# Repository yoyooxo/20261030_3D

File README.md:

# 20261030_3D — 讀卡機（單顆 nRF52840＋健保卡卡座）

只用一顆 nRF52840 模組（nice!nano v2 腳位）接 ISO 7816 卡座，焊在一塊 11 × 24 孔的洞洞板上。
卡座在板子背面、插卡口在上，模組的 USB-C 朝下，線全部在正面用 OK 線手焊，電池最後用雙面膠黏。

目前版本是 v7。

## 規格

| 項目 | 內容 |
|---|---|
| 洞洞板 | 27.9 × 61 mm，11 × 24 孔，2.54 mm 間距，直放 |
| 孔位標示 | (欄 c, 列 r)：c 為 1–11（左→右），r 為 1–24（下→上），正面俯視 |
| 卡座 J1 | 約 62 × 40 mm，在板子背面，上緣是插卡口；8 支腳焊進 c8–c11 的第 24 列和第 8 列 |
| 模組 U1 | 腳在 c1、c7 的第 1–12 列，轉 180°，USB-C 從板子下緣凸出；每邊 13 孔，最靠 USB 那對 B+ / B- 在板子外 |
| C10 | 0.1 µF，c8、c9 的第 6 列 |
| 電池 | LiPo 約 13 × 23 mm（照片估），在模組右邊，蓋在線上面 |

## 卡座腳位

| 位置 | c8 | c9 | c10 | c11 |
|---|---|---|---|---|
| 插卡口那排（第 24 列） | C5 GND | C6 | C7 I/O | C8 |
| 對面那排（第 8 列） | C1 VCC | C2 RST | C3 CLK | C4 |

C4、C6、C8 不接線，腳還是焊進洞，用來固定卡座。

## 接線（全部走正面，用 OK 線）

| 線號 | 起點 | 終點 | 用途 |
|---|---|---|---|
| K1 | VCC (c1,r4) | J1 C1 VCC (c8,r8) | +3V3_CARD，跨過模組，途中接 C10 |
| K2 | GND (c7,r3) | J1 C5 GND (c8,r24) | 卡片 GND |
| K3 | P0.24 (c7,r8) | J1 C2 RST (c9,r8) | RST |
| K4 | P0.17 (c7,r5) | J1 C3 CLK (c10,r8) | CLK |
| K5 | P0.22 (c7,r7) | J1 C7 I/O (c10,r24) | I/O |
| K6 | P0.20 (c7,r6) | P0.22 (c7,r7) | I/O 兩腳併接 |
| K7 | GND (c7,r3) | GND (c7,r4) | GND 兩腳併接 |
| K10 | GND (c7,r4) | C10 GND 腳 (c9,r6) | C10 接地 |
| K8 | P1.00 (c7,r9) | J1 SW1 DET | 插卡偵測（選配） |
| K9 | J1 SW2 DET_G | C10 GND 腳 (c9,r6) | 偵測開關接地（選配） |
| K11 | 電池 ＋ | RAW (c1,r1) | VBAT |
| K12 | 電池 － | GND (c1,r2) | 電池負極 |

卡片的 VCC 由模組上的 MOSFET 開關（P0.13 / EXT_POWER），所以可以斷電重開卡片。

## 還沒確定的

| 項目 | 目前做法 | 怎麼確認 |
|---|---|---|
| C1–C8 的左右順序 | 照實物照片的接線判斷 | 焊之前用電表量 |
| 插卡口在哪一排 | 放上面 | 實際插卡看 |
| 偵測開關 SW1 / SW2 的腳位 | 畫在板子右緣外、第 8 列旁邊 | 看卡座實物 |
| 電池大小 | 約 13 × 23 mm | 量電池 |

## 檔案

| 檔案 | 用途 |
|---|---|
| [`card_reader_nicenano/讀卡機Layout_v7.png`](card_reader_nicenano/讀卡機Layout_v7.png) / [`.svg`](card_reader_nicenano/讀卡機Layout_v7.svg) | 目前的 Layout（含接線表） |
| `card_reader_nicenano/gen_layout_card7.py` | 產生 v7 圖的程式 |
| [`card_reader_nicenano/讀卡機_整理.md`](card_reader_nicenano/讀卡機_整理.md) | 整理筆記（內容寫到 v6） |
| `card_reader_nicenano/` 其他檔案 | v1–v6 的舊版 Layout 和程式，保留參考 |

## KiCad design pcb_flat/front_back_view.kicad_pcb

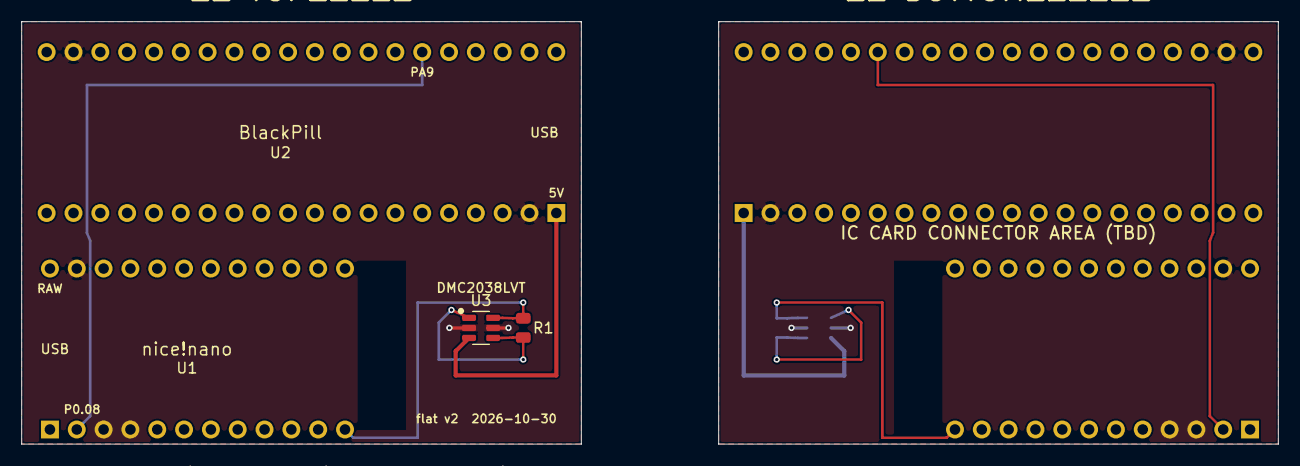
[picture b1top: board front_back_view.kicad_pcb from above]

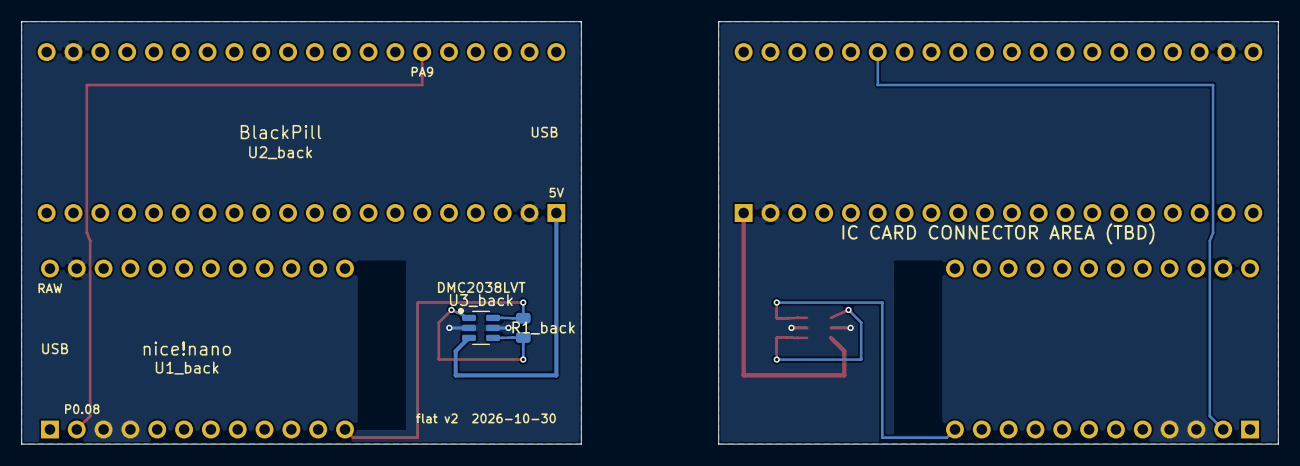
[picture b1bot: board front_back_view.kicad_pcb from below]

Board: 2 copper layers, 119.0 x 40.0 mm, 10 parts (5 on the bottom side), 5 nets.

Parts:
BT1, BT1_back: LiPo_30x25x5_on_BlackPill
R1, R1_back: R_0805
U1, U1_back: nice!nano_v2
U2, U2_back: WeAct_BlackPill
U3, U3_back: DMC2038LVT_SOT-23-6

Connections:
+5V: U2.L1, U2_back.L1, U3.3, U3_back.3
GND: U1.3, U1.4, U1.23, U1_back.3, U1_back.4, U1_back.23, U2.H19, U2.L2, U2_back.H19, U2_back.L2, U3.2, U3.5, U3_back.2, U3_back.5
N_D1: R1.2, R1_back.2, U1.12, U1_back.12, U3.6, U3_back.6
N_G1_D2: R1.1, R1_back.1, U3.1, U3.4, U3_back.1, U3_back.4
UART_PA9_P0.08: U1.2, U1_back.2, U2.H6, U2_back.H6

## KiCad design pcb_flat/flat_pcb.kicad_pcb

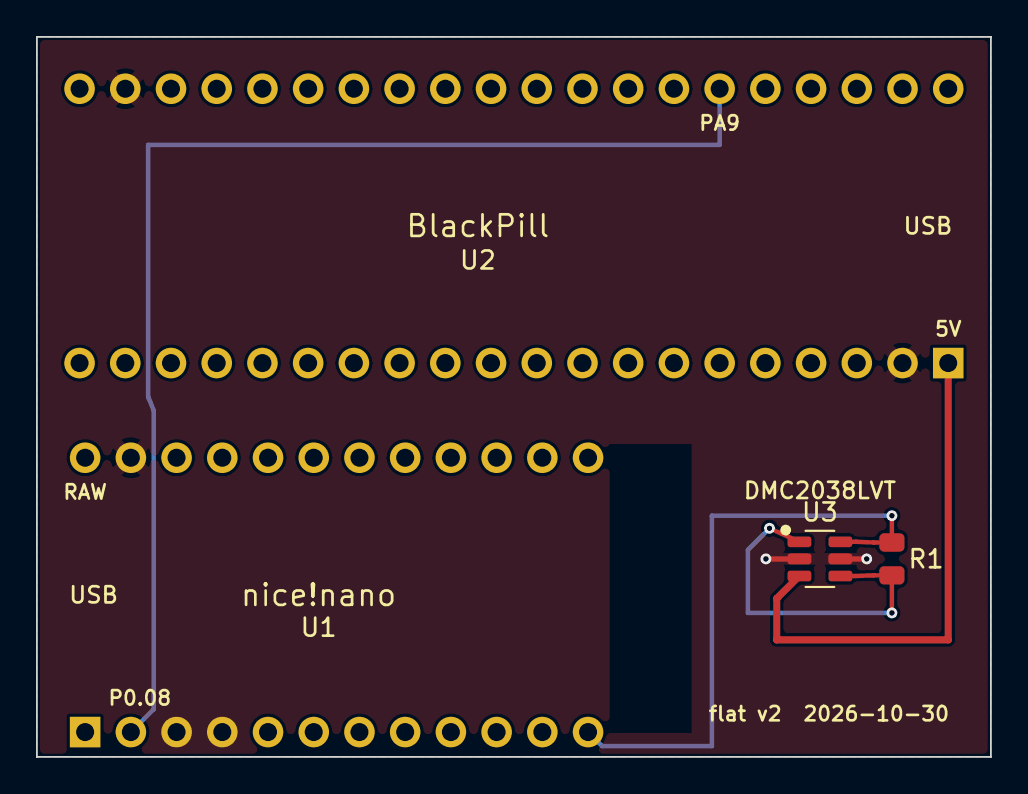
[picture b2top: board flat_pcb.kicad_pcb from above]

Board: 2 copper layers, 53.0 x 40.0 mm, 5 parts (0 on the bottom side), 5 nets.

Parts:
BT1: LiPo_30x25x5_on_BlackPill
R1: R_0805
U1: nice!nano_v2
U2: WeAct_BlackPill
U3: DMC2038LVT_SOT-23-6

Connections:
+5V: U2.L1, U3.3
GND: U1.3, U1.4, U1.23, U2.H19, U2.L2, U3.2, U3.5
N_D1: R1.2, U1.12, U3.6
N_G1_D2: R1.1, U3.1, U3.4
UART_PA9_P0.08: U1.2, U2.H6
